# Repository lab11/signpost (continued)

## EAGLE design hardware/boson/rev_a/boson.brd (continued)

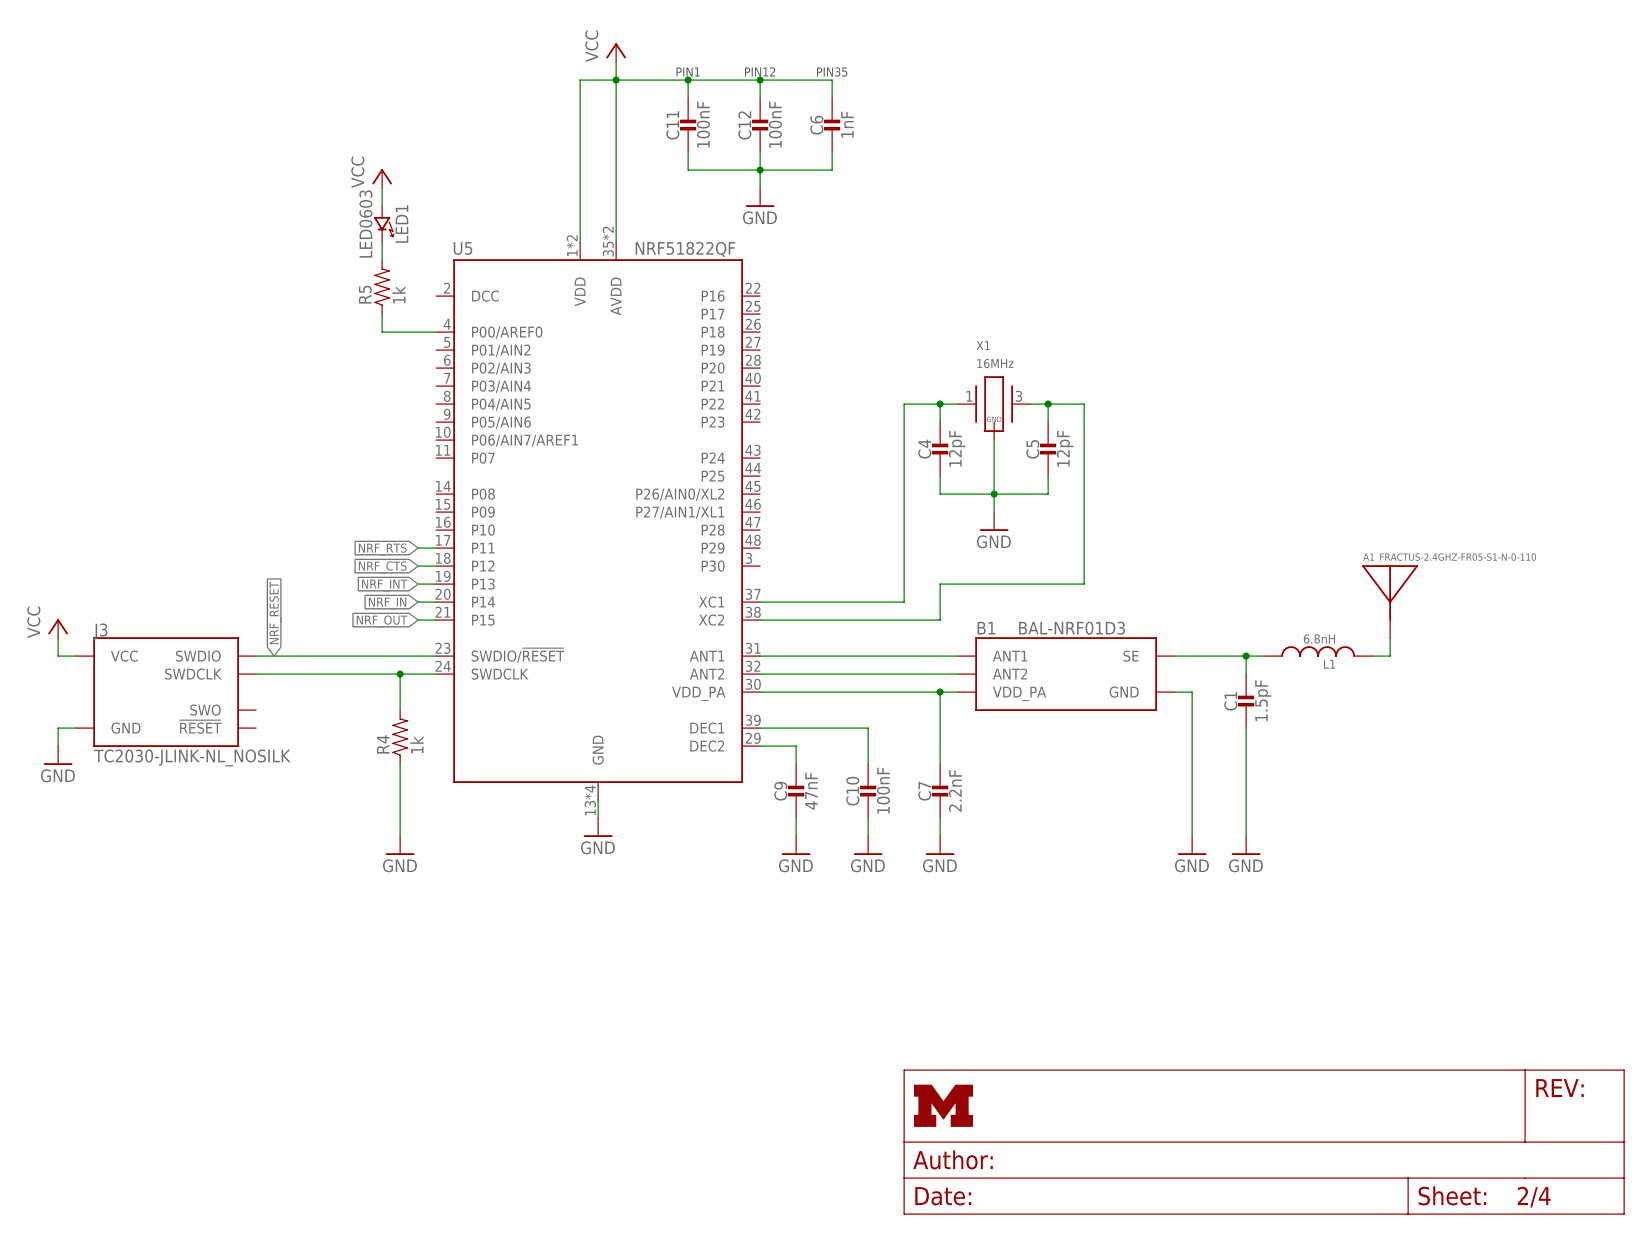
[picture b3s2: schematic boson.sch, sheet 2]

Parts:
A1: FRACTUS-2.4GHZ-FR05-S1-N-0-110; FRACTUS-ANTENNA-FR05-S1-N-0-110
B1: BAL-NRF01D3
C1: 1.5pF; 0402_CAP
C4, C5: 12pF; 0402_CAP; DIGIKEY 490-6197-1-ND
C6: 1nF; 0402_CAP
C7: 2.2nF; 0402_CAP
C9: 47nF; 0402_CAP
C10, C11, C12: 100nF; 0402_CAP
J3: TC2030-JLINK-NL_NOSILK; TC2030-IDC-NL_NOSILK
L1: 6.8nH; 0402_CAP
LED1: LED0603; LED-0603
R4, R5: 1k; 0402_RES
U5: NRF51822QF; QFN-48-6MM
X1: 16MHz; TXC-8Y; DIGIKEY 887-2003-1-ND

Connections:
!NRF_RESET: J3.2 (SWDIO), U5.23 (SWDIO/!RESET); also elsewhere on the board
GND: B1.GND, C1.2, C4.2, C5.2, C6.2, C7.2, C9.2, C10.2, C11.2, C12.2, J3.5 (GND), R4.1, U5.13 (GND), U5.33 (GND), U5.34 (GND), U5.GND, X1.2 (GND), X1.4 (GND); also elsewhere on the board
unnamed: C10.1, U5.39 (DEC1)
unnamed: C9.1, U5.29 (DEC2)
unnamed: J3.4 (SWDCLK), R4.2, U5.24 (SWDCLK)
unnamed: R5.1, U5.4 (P00/AREF0)
unnamed: LED1.C (CATHODE), R5.2
unnamed: B1.ANT1, U5.31 (ANT1)
unnamed: B1.VCC (VDD_PA), C7.1, U5.30 (VDD_PA)
unnamed: B1.ANT2, U5.32 (ANT2)
unnamed: C4.1, U5.37 (XC1), X1.1
unnamed: C5.1, U5.38 (XC2), X1.3 (2)
unnamed: B1.SE, C1.1, L1.1
unnamed: A1.ANT, L1.2
NRF_CTS: U5.18 (P12); also elsewhere on the board
NRF_IN: U5.20 (P14); also elsewhere on the board
NRF_INT: U5.19 (P13); also elsewhere on the board
NRF_OUT: U5.21 (P15); also elsewhere on the board
NRF_RTS: U5.17 (P11); also elsewhere on the board
VCC: C6.1, C11.1, C12.1, J3.1 (VCC), LED1.A (ANODE), U5.1 (VDD), U5.12 (VDD), U5.35 (AVDD), U5.36 (AVDD); also elsewhere on the board

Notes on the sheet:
PIN35
PIN1
PIN12

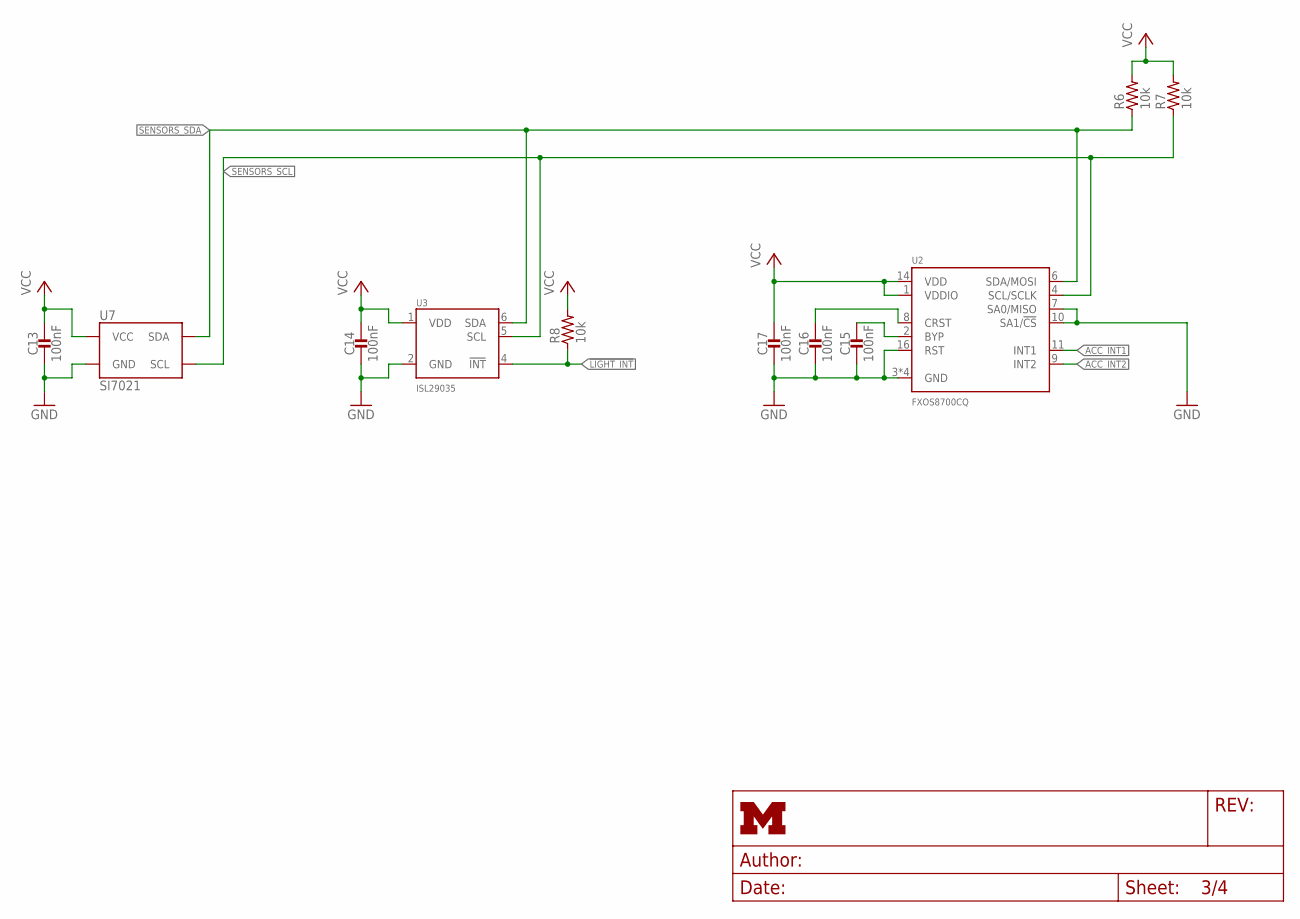
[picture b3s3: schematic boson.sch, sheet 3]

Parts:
C13, C14, C15, C16, C17: 100nF; 0402_CAP
R6, R7, R8: 10k; 0402_RES
U2: FXOS8700CQ; QFN-16-3MM
U3: ISL29035; ODFN-6-1.5MMX1.6MM
U7: SI7021; DFN-6/3MM

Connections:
!LIGHT_INT: R8.1, U3.4 (!INT); also elsewhere on the board
ACC_INT1: U2.11 (INT1); also elsewhere on the board
ACC_INT2: U2.9 (INT2); also elsewhere on the board
GND: C13.2, C14.2, C15.2, C16.2, C17.2, U2.3 (GND), U2.5 (GND), U2.7 (SA0/MISO), U2.10 (SA1/!CS), U2.12 (GND), U2.13 (GND), U2.16 (RST), U3.2 (GND), U7.2 (GND); also elsewhere on the board
unnamed: C15.1, U2.2 (BYP)
unnamed: C16.1, U2.8 (CRST)
SENSORS_SCL: R7.1, U2.4 (SCL/SCLK), U3.5 (SCL), U7.6 (SCL); also elsewhere on the board
SENSORS_SDA: R6.1, U2.6 (SDA/MOSI), U3.6 (SDA), U7.1 (SDA); also elsewhere on the board
VCC: C13.1, C14.1, C17.1, R6.2, R7.2, R8.2, U2.1 (VDDIO), U2.14 (VDD), U3.1 (VDD), U7.5 (VCC); also elsewhere on the board

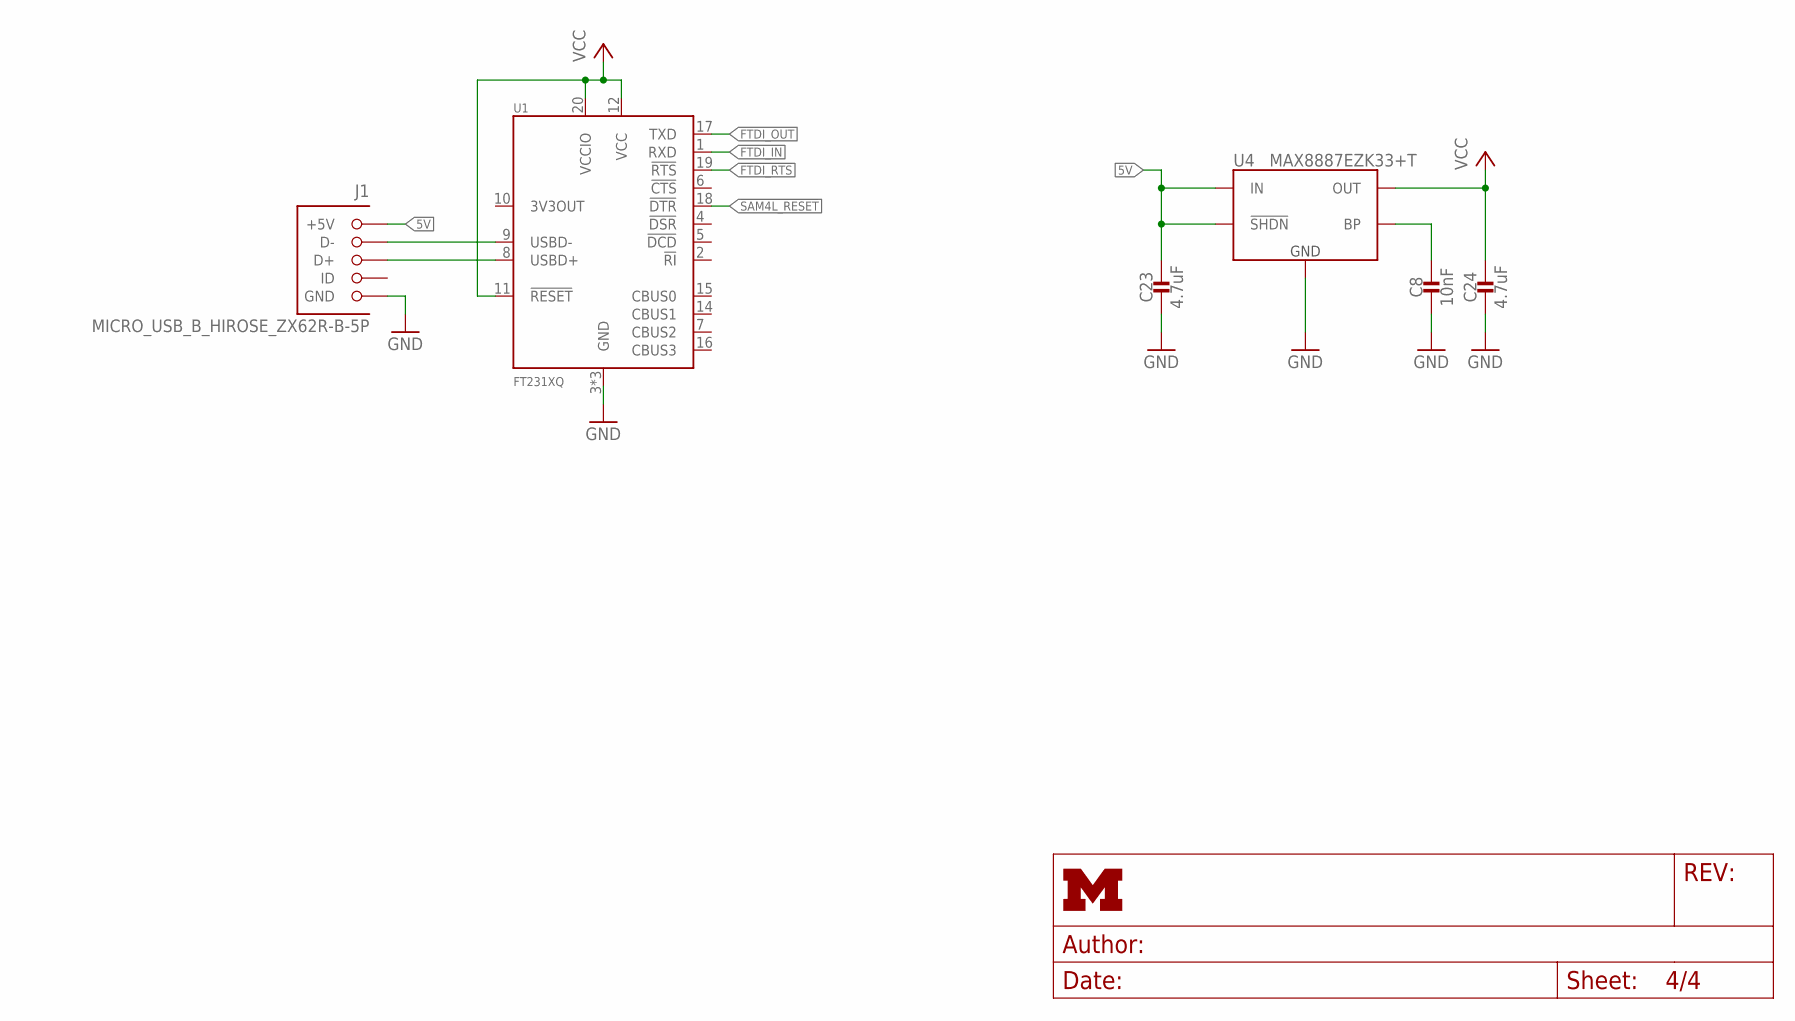
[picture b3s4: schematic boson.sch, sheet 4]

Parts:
C8: 10nF; 0402_CAP
C23, C24: 4.7uF; 0402_CAP
J1: MICRO_USB_B_HIROSE_ZX62R-B-5P; USB_MICRO_B-HIROSE-ZX62R-B-5P; DIGIKEY H125274CT-ND
U1: FT231XQ; QFN-20-4MM
U4: MAX8887EZK33+T; SOT-23-5

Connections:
5V: C23.1, J1.1 (+5V), U4.1 (IN), U4.3 (!SHDN); also elsewhere on the board
!FTDI_RTS: U1.19 (!RTS); also elsewhere on the board
!SAM4L_RESET: U1.18 (!DTR); also elsewhere on the board
FTDI_IN: U1.1 (RXD); also elsewhere on the board
FTDI_OUT: U1.17 (TXD); also elsewhere on the board
GND: C8.2, C23.2, C24.2, J1.5 (GND), U1.3 (GND), U1.13 (GND), U1.GND, U4.2 (GND); also elsewhere on the board
unnamed: J1.2 (D-), U1.9 (USBD-)
unnamed: J1.3 (D+), U1.8 (USBD+)
unnamed: C8.1, U4.4 (BP)
VCC: C24.1, U1.11 (!RESET), U1.12 (VCC), U1.20 (VCCIO), U4.5 (OUT); also elsewhere on the board

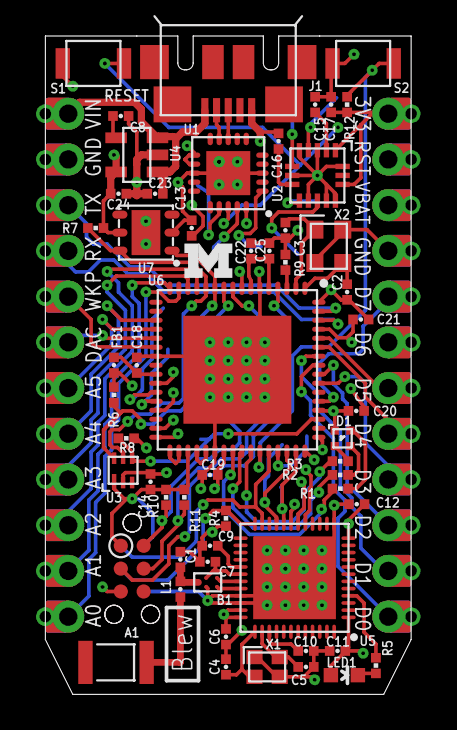
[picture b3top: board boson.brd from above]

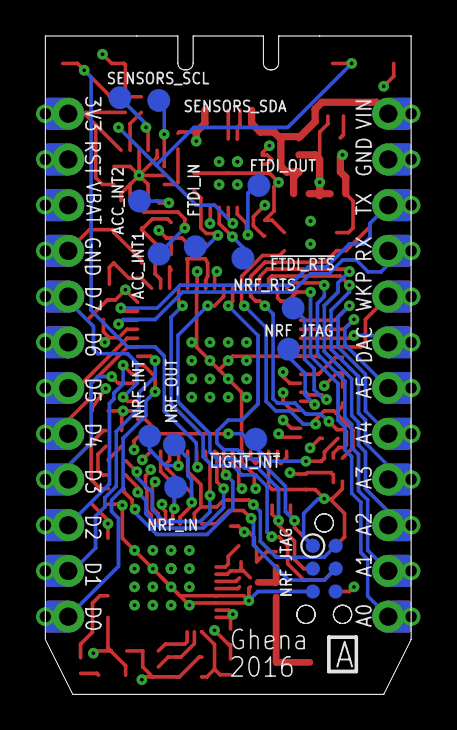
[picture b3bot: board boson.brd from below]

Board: 4 copper layers, 20.3 x 36.6 mm, 75 parts (14 on the bottom side), 69 nets.

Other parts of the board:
U$1: PHOTON-BOTTOM-SS
U$2: PHOTON-TOP-SS
U$3: UMICH_SOLID_75MIL

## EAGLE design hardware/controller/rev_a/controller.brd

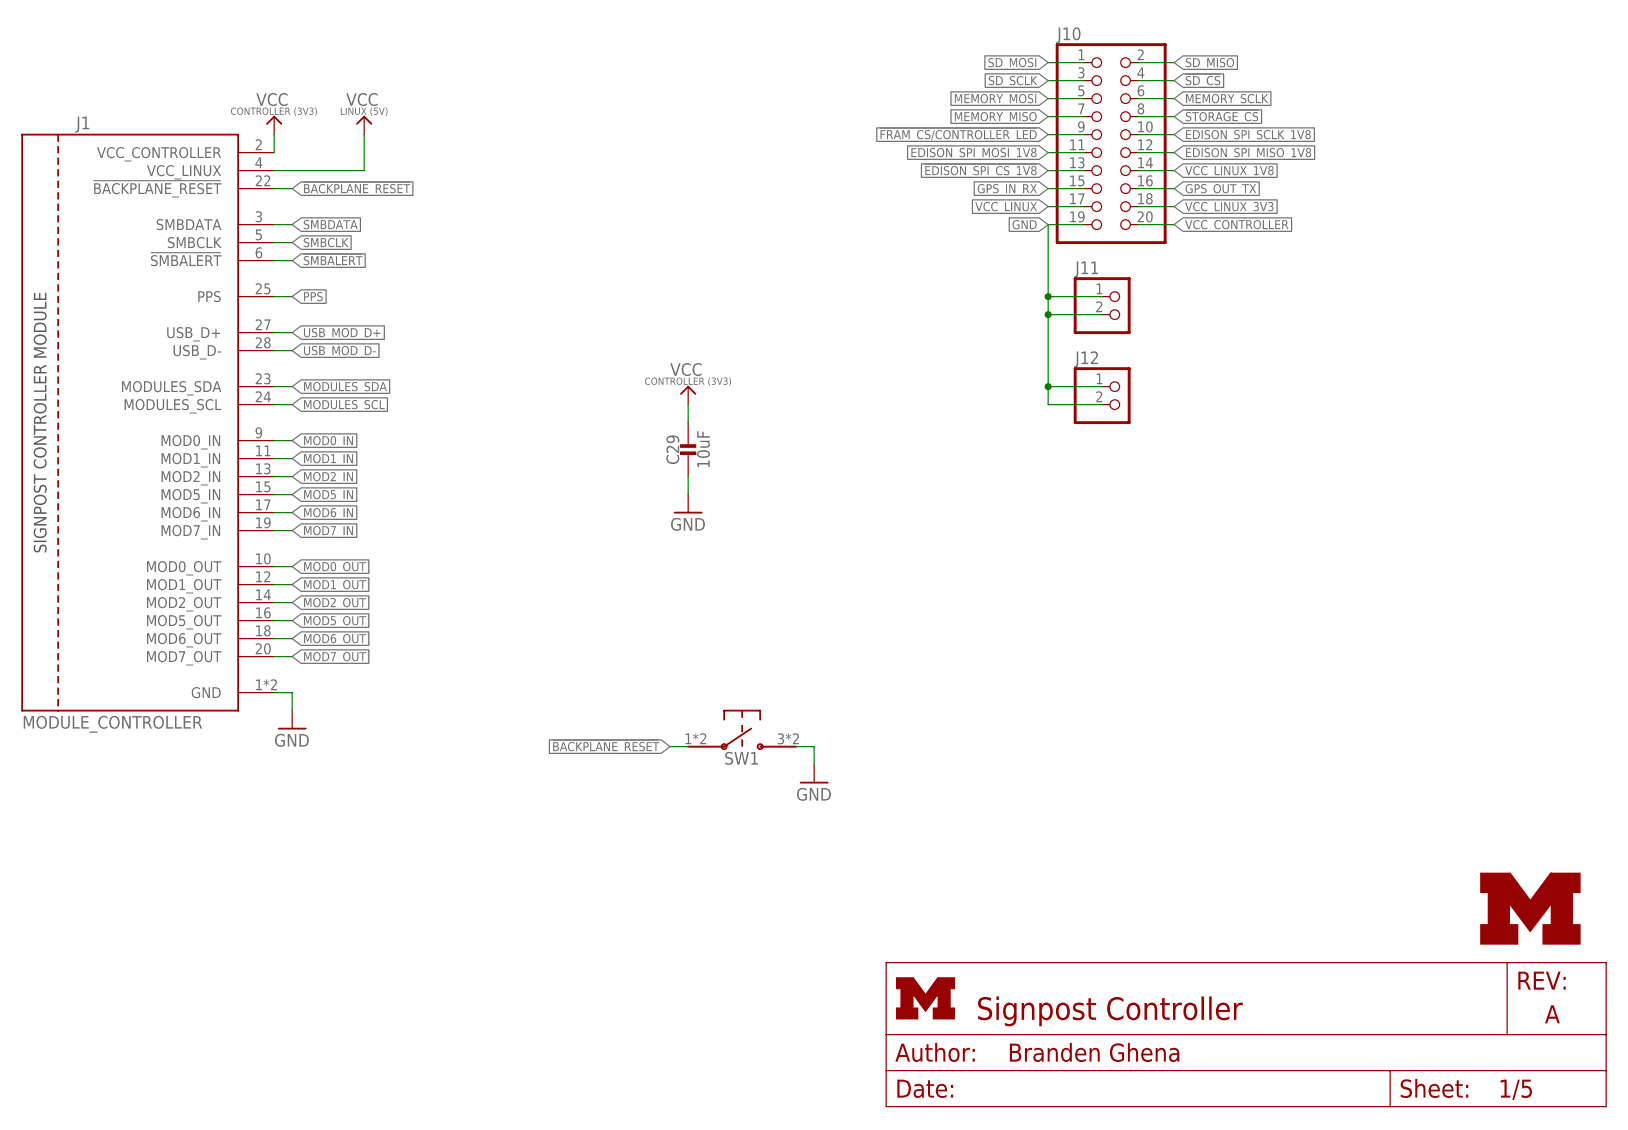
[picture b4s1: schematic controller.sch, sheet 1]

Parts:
C29: 10uF; 0402_CAP; DIGIKEY 490-13811-1-ND
J1: MODULE_CONTROLLER
J10: PINHD-2X10; 2X10
J11, J12: PINHD-1X2; 1X02
LOGO1: UMICH_SOLID_MEDIUM; UMICH_SOLID_200MIL
SW1: PTS810SJ

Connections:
!BACKPLANE_RESET: J1.22 (!BACKPLANE_RESET), SW1.1, SW1.2
!EDISON_SPI_CS_1V8: J10.13; also elsewhere on the board
!FRAM_CS/CONTROLLER_LED: J10.9; also elsewhere on the board
!SD_CS: J10.4; also elsewhere on the board
!SMBALERT: J1.6 (!SMBALERT); also elsewhere on the board
!STORAGE_CS: J10.8; also elsewhere on the board
EDISON_SPI_MISO_1V8: J10.12; also elsewhere on the board
EDISON_SPI_MOSI_1V8: J10.11; also elsewhere on the board
EDISON_SPI_SCLK_1V8: J10.10; also elsewhere on the board
GND: C29.2, J1.1 (GND), J1.21 (GND), J10.19, J11.1, J11.2, J12.1, J12.2, SW1.3, SW1.4; also elsewhere on the board
GPS_IN_RX: J10.15; also elsewhere on the board
GPS_OUT_TX: J10.16; also elsewhere on the board
MEMORY_MISO: J10.7; also elsewhere on the board
MEMORY_MOSI: J10.5; also elsewhere on the board
MEMORY_SCLK: J10.6; also elsewhere on the board
MOD0_IN: J1.9 (MOD0_IN); also elsewhere on the board
MOD0_OUT: J1.10 (MOD0_OUT); also elsewhere on the board
MOD1_IN: J1.11 (MOD1_IN); also elsewhere on the board
MOD1_OUT: J1.12 (MOD1_OUT); also elsewhere on the board
MOD2_IN: J1.13 (MOD2_IN); also elsewhere on the board
MOD2_OUT: J1.14 (MOD2_OUT); also elsewhere on the board
MOD5_IN: J1.15 (MOD5_IN); also elsewhere on the board
MOD5_OUT: J1.16 (MOD5_OUT); also elsewhere on the board
MOD6_IN: J1.17 (MOD6_IN); also elsewhere on the board
MOD6_OUT: J1.18 (MOD6_OUT); also elsewhere on the board
MOD7_IN: J1.19 (MOD7_IN); also elsewhere on the board
MOD7_OUT: J1.20 (MOD7_OUT); also elsewhere on the board
MODULES_SCL: J1.24 (MODULES_SCL); also elsewhere on the board
MODULES_SDA: J1.23 (MODULES_SDA); also elsewhere on the board
PPS: J1.25 (PPS); also elsewhere on the board
SD_MISO: J10.2; also elsewhere on the board
SD_MOSI: J10.1; also elsewhere on the board
SD_SCLK: J10.3; also elsewhere on the board
SMBCLK: J1.5 (SMBCLK); also elsewhere on the board
SMBDATA: J1.3 (SMBDATA); also elsewhere on the board
USB_MOD_D+: J1.27 (USB_D+); also elsewhere on the board
USB_MOD_D-: J1.28 (USB_D-); also elsewhere on the board
VCC_CONTROLLER: C29.1, J1.2 (VCC_CONTROLLER), J10.20; also elsewhere on the board
VCC_LINUX: J1.4 (VCC_LINUX), J10.17; also elsewhere on the board
VCC_LINUX_1V8: J10.14; also elsewhere on the board
VCC_LINUX_3V3: J10.18; also elsewhere on the board

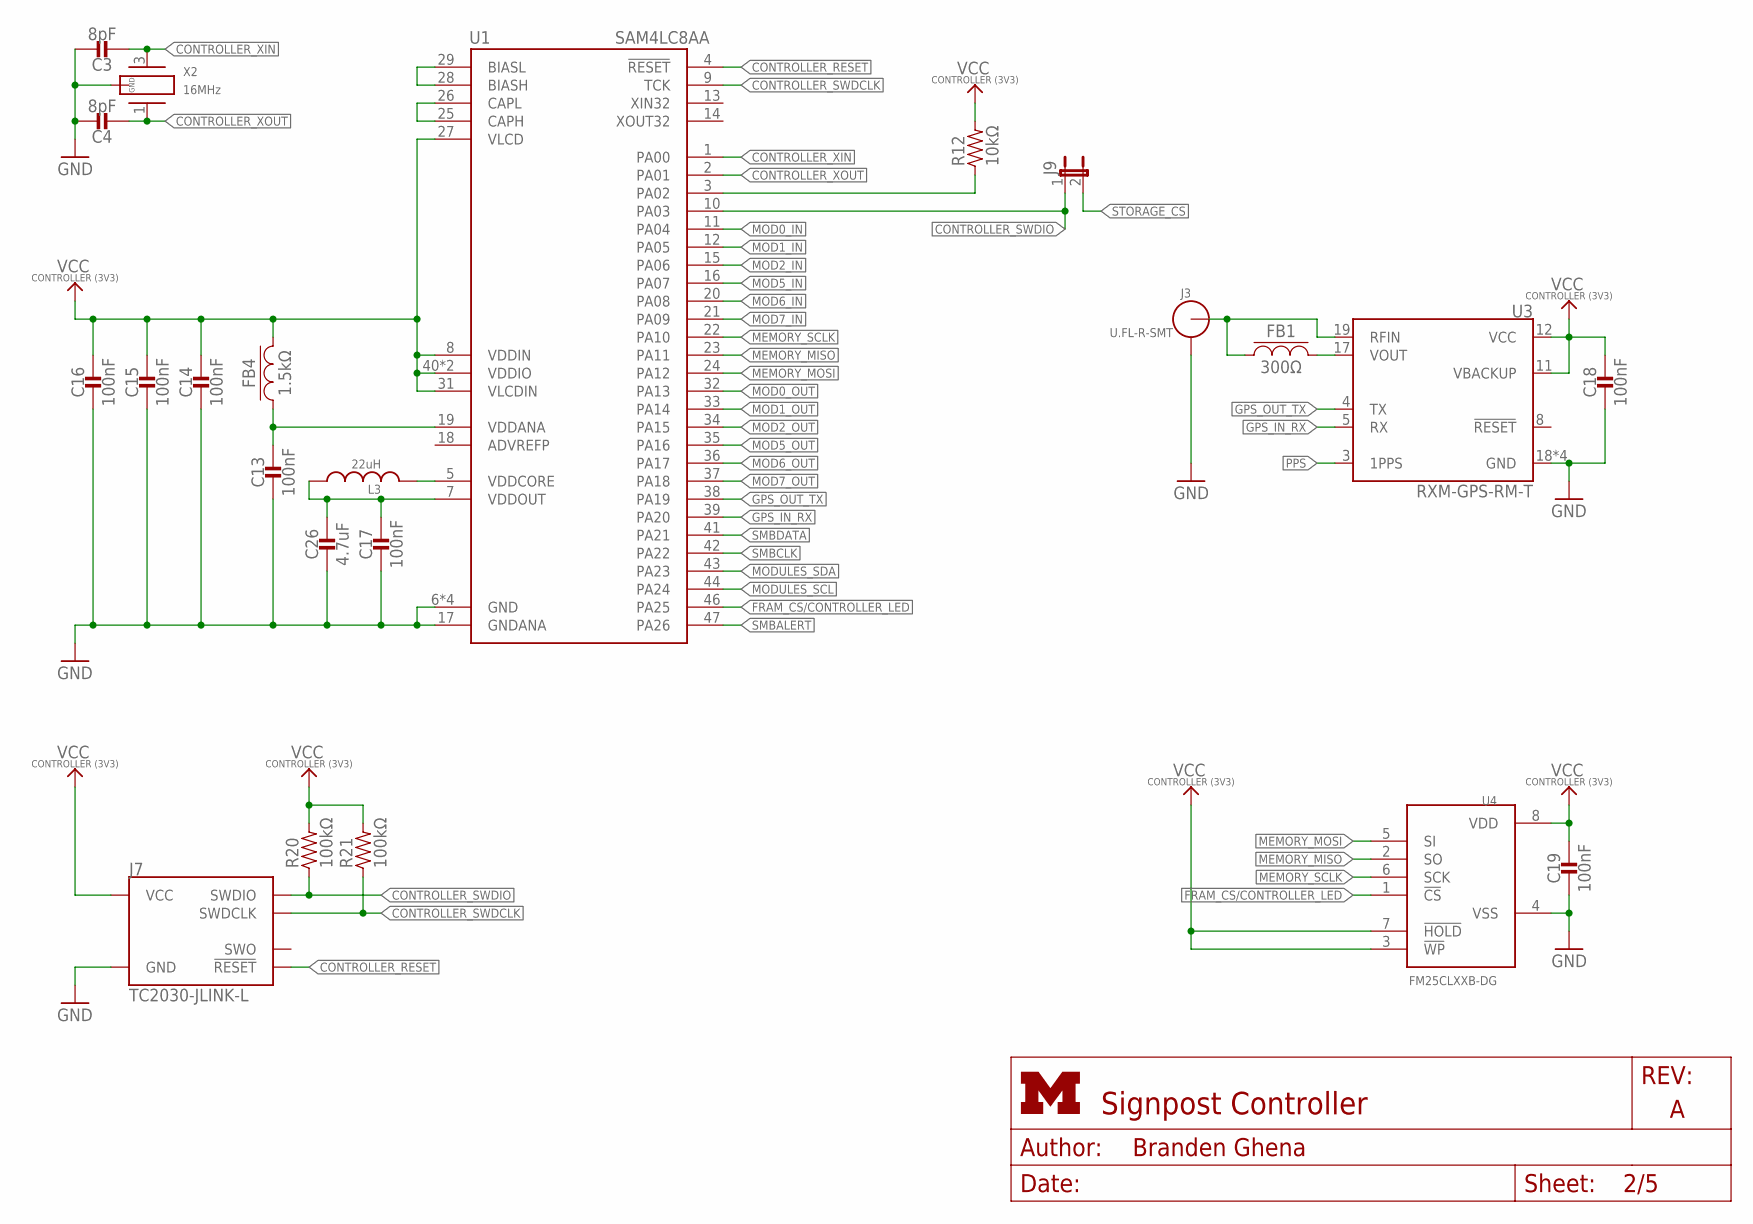
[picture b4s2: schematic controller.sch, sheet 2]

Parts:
C3, C4: 8pF; 0402_CAP; DIGIKEY 490-8230-1-ND
C13, C14, C15, C16, C17, C18, C19: 100nF; 0402_CAP; DIGIKEY 490-10777-1-ND
C26: 4.7uF; 0402_CAP; DIGIKEY 490-13252-1-ND
FB1: 300Ω; 0402_CAP; DIGIKEY ACML-0402-301-TCT-ND
FB4: 1.5kΩ; 0402_CAP; DIGIKEY 490-5216-1-ND
J3: U.FL-R-SMT; U.FL_SMT
J7: TC2030-JLINK-L; TC2030-IDC
J9: JUMPER-2PTH; 1X02
L3: 22uH; 1212
R12: 10kΩ; 0402_RES; DIGIKEY 1276-3431-1-ND
R20, R21: 100kΩ; 0402_RES; DIGIKEY 1276-3432-1-ND
U1: SAM4LC8AA; QFN-48-7MM
U3: RXM-GPS-RM-T
U4: FM25CLXXB-DG; TDFN-8; DIGIKEY FM25CL64B-DGRA-ND
X2: 16MHz; FHXXX

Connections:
!CONTROLLER_RESET: J7.3 (!RESET), U1.4 (!RESET)
!FRAM_CS/CONTROLLER_LED: U1.46 (PA25), U4.1 (!CS); also elsewhere on the board
!SMBALERT: U1.47 (PA26); also elsewhere on the board
!STORAGE_CS: J9.2; also elsewhere on the board
CONTROLLER_BUCK/LDO_N: R12.1, U1.3 (PA02)
CONTROLLER_SWDCLK: J7.4 (SWDCLK), R21.1, U1.9 (TCK)
CONTROLLER_SWDIO: J7.2 (SWDIO), J9.1, R20.1, U1.10 (PA03)
CONTROLLER_XIN: C3.1, U1.1 (PA00), X2.3 (2)
CONTROLLER_XOUT: C4.1, U1.2 (PA01), X2.1
GND: C3.2, C4.2, C13.2, C14.2, C15.2, C16.2, C17.2, C18.2, C19.2, C26.2, J3.GND1, J3.GND2, J7.5 (GND), U1.6 (GND), U1.17 (GNDANA), U1.30 (GND), U1.48 (GND), U1.THERMAL (GND), U3.18 (GND), U3.20 (GND), U3.21 (GND), U3.22 (GND), U4.4 (VSS), X2.2 (GND), X2.4 (GND); also elsewhere on the board
GPS_IN_RX: U1.39 (PA20), U3.5 (RX); also elsewhere on the board
GPS_OUT_TX: U1.38 (PA19), U3.4 (TX); also elsewhere on the board
MEMORY_MISO: U1.23 (PA11), U4.2 (SO); also elsewhere on the board
MEMORY_MOSI: U1.24 (PA12), U4.5 (SI); also elsewhere on the board
MEMORY_SCLK: U1.22 (PA10), U4.6 (SCK); also elsewhere on the board
MOD0_IN: U1.11 (PA04); also elsewhere on the board
MOD0_OUT: U1.32 (PA13); also elsewhere on the board
MOD1_IN: U1.12 (PA05); also elsewhere on the board
MOD1_OUT: U1.33 (PA14); also elsewhere on the board
MOD2_IN: U1.15 (PA06); also elsewhere on the board
MOD2_OUT: U1.34 (PA15); also elsewhere on the board
MOD5_IN: U1.16 (PA07); also elsewhere on the board
MOD5_OUT: U1.35 (PA16); also elsewhere on the board
MOD6_IN: U1.20 (PA08); also elsewhere on the board
MOD6_OUT: U1.36 (PA17); also elsewhere on the board
MOD7_IN: U1.21 (PA09); also elsewhere on the board
MOD7_OUT: U1.37 (PA18); also elsewhere on the board
MODULES_SCL: U1.44 (PA24); also elsewhere on the board
MODULES_SDA: U1.43 (PA23); also elsewhere on the board
unnamed: FB1.1, U3.17 (VOUT)
unnamed: FB1.2, J3.SIG (ANT), U3.19 (RFIN)
unnamed: C13.1, FB4.1, U1.19 (VDDANA)
unnamed: C17.1, C26.1, L3.P$1 (1), U1.7 (VDDOUT)
unnamed: L3.P$2 (2), U1.5 (VDDCORE)
unnamed: U1.28 (BIASH), U1.29 (BIASL)
unnamed: U1.25 (CAPH), U1.26 (CAPL)
PPS: U3.3 (1PPS); also elsewhere on the board
SMBCLK: U1.42 (PA22); also elsewhere on the board
SMBDATA: U1.41 (PA21); also elsewhere on the board
VCC_CONTROLLER: C14.1, C15.1, C16.1, C18.1, C19.1, FB4.2, J7.1 (VCC), R12.2, R20.2, R21.2, U1.8 (VDDIN), U1.27 (VLCD), U1.31 (VLCDIN), U1.40 (VDDIO), U1.45 (VDDIO), U3.11 (VBACKUP), U3.12 (VCC), U4.3 (!WP), U4.7 (!HOLD), U4.8 (VDD); also elsewhere on the board

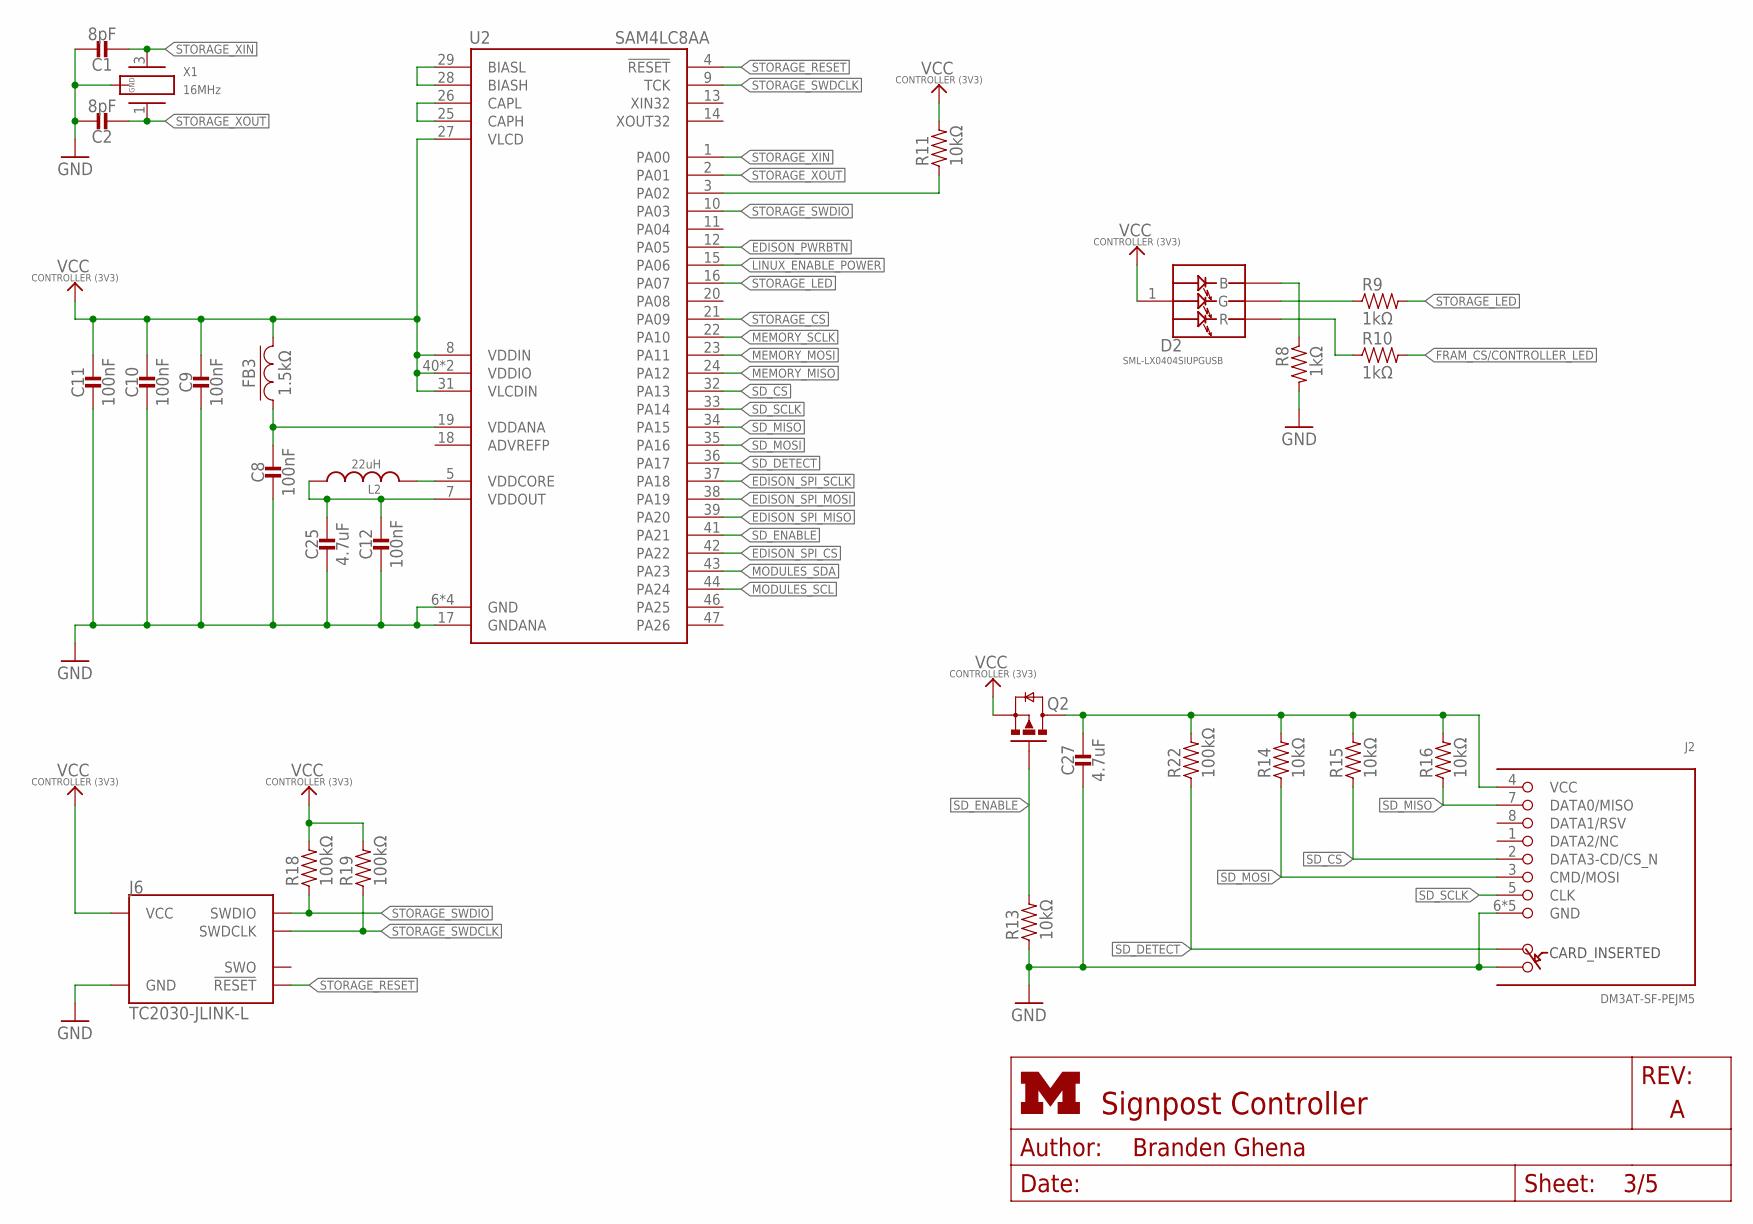
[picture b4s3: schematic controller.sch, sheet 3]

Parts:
C1, C2: 8pF; 0402_CAP; DIGIKEY 490-8230-1-ND
C8, C9, C10, C11, C12: 100nF; 0402_CAP; DIGIKEY 490-10777-1-ND
C25, C27: 4.7uF; 0402_CAP; DIGIKEY 490-13252-1-ND
D2: SML-LX0404SIUPGUSB; 1MM_SQ_4PAD
FB3: 1.5kΩ; 0402_CAP; DIGIKEY 490-5216-1-ND
J2: DM3AT-SF-PEJM5
J6: TC2030-JLINK-L; TC2030-IDC
L2: 22uH; 1212
Q2: NX3008PBK; SOT23-3
R8, R9, R10: 1kΩ; 0402_RES; DIGIKEY 1276-3430-1-ND
R11, R13, R14, R15, R16: 10kΩ; 0402_RES; DIGIKEY 1276-3431-1-ND
R18, R19, R22: 100kΩ; 0402_RES; DIGIKEY 1276-3432-1-ND
U2: SAM4LC8AA; QFN-48-7MM
X1: 16MHz; FHXXX

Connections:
!EDISON_PWRBTN: U2.12 (PA05); also elsewhere on the board
!EDISON_SPI_CS: U2.42 (PA22); also elsewhere on the board
!FRAM_CS/CONTROLLER_LED: R10.2; also elsewhere on the board
!SD_CS: J2.2 (DATA3-CD/CS_N), R15.1, U2.32 (PA13); also elsewhere on the board
!STORAGE_CS: U2.21 (PA09); also elsewhere on the board
!STORAGE_LED: R9.2, U2.16 (PA07)
!STORAGE_RESET: J6.3 (!RESET), U2.4 (!RESET)
EDISON_SPI_MISO: U2.39 (PA20); also elsewhere on the board
EDISON_SPI_MOSI: U2.38 (PA19); also elsewhere on the board
EDISON_SPI_SCLK: U2.37 (PA18); also elsewhere on the board
GND: C1.2, C2.2, C8.2, C9.2, C10.2, C11.2, C12.2, C25.2, C27.2, J2.6 (GND), J2.B, J2.MOUNT0 (GND), J2.MOUNT1 (GND), J2.MOUNT2 (GND), J2.MOUNT3 (GND), J6.5 (GND), R8.2, R13.1, U2.6 (GND), U2.17 (GNDANA), U2.30 (GND), U2.48 (GND), U2.THERMAL (GND), X1.2 (GND), X1.4 (GND); also elsewhere on the board
LINUX_ENABLE_POWER: U2.15 (PA06); also elsewhere on the board
MEMORY_MISO: U2.24 (PA12); also elsewhere on the board
MEMORY_MOSI: U2.23 (PA11); also elsewhere on the board
MEMORY_SCLK: U2.22 (PA10); also elsewhere on the board
MODULES_SCL: U2.44 (PA24); also elsewhere on the board
MODULES_SDA: U2.43 (PA23); also elsewhere on the board
unnamed: D2.3 (B), R8.1
unnamed: D2.4 (G), R9.1
unnamed: D2.2 (R), R10.1
unnamed: C27.1, J2.4 (VCC), Q2.3 (D), R14.2, R15.2, R16.2, R22.2
unnamed: C8.1, FB3.1, U2.19 (VDDANA)
unnamed: C12.1, C25.1, L2.P$1 (1), U2.7 (VDDOUT)
unnamed: L2.P$2 (2), U2.5 (VDDCORE)
unnamed: U2.25 (CAPH), U2.26 (CAPL)
unnamed: U2.28 (BIASH), U2.29 (BIASL)
SD_DETECT: J2.A, R22.1, U2.36 (PA17)
SD_ENABLE: Q2.1 (G), R13.2, U2.41 (PA21)
SD_MISO: J2.7 (DATA0/MISO), R16.1, U2.34 (PA15); also elsewhere on the board
SD_MOSI: J2.3 (CMD/MOSI), R14.1, U2.35 (PA16); also elsewhere on the board
SD_SCLK: J2.5 (CLK), U2.33 (PA14); also elsewhere on the board
STORAGE_BUCK/LDO_N: R11.1, U2.3 (PA02)
STORAGE_SWDCLK: J6.4 (SWDCLK), R19.1, U2.9 (TCK)
STORAGE_SWDIO: J6.2 (SWDIO), R18.1, U2.10 (PA03)
STORAGE_XIN: C1.1, U2.1 (PA00), X1.3 (2)
STORAGE_XOUT: C2.1, U2.2 (PA01), X1.1
VCC_CONTROLLER: C9.1, C10.1, C11.1, D2.1 (VDD), FB3.2, J6.1 (VCC), Q2.2 (S), R11.2, R18.2, R19.2, U2.8 (VDDIN), U2.27 (VLCD), U2.31 (VLCDIN), U2.40 (VDDIO), U2.45 (VDDIO); also elsewhere on the board

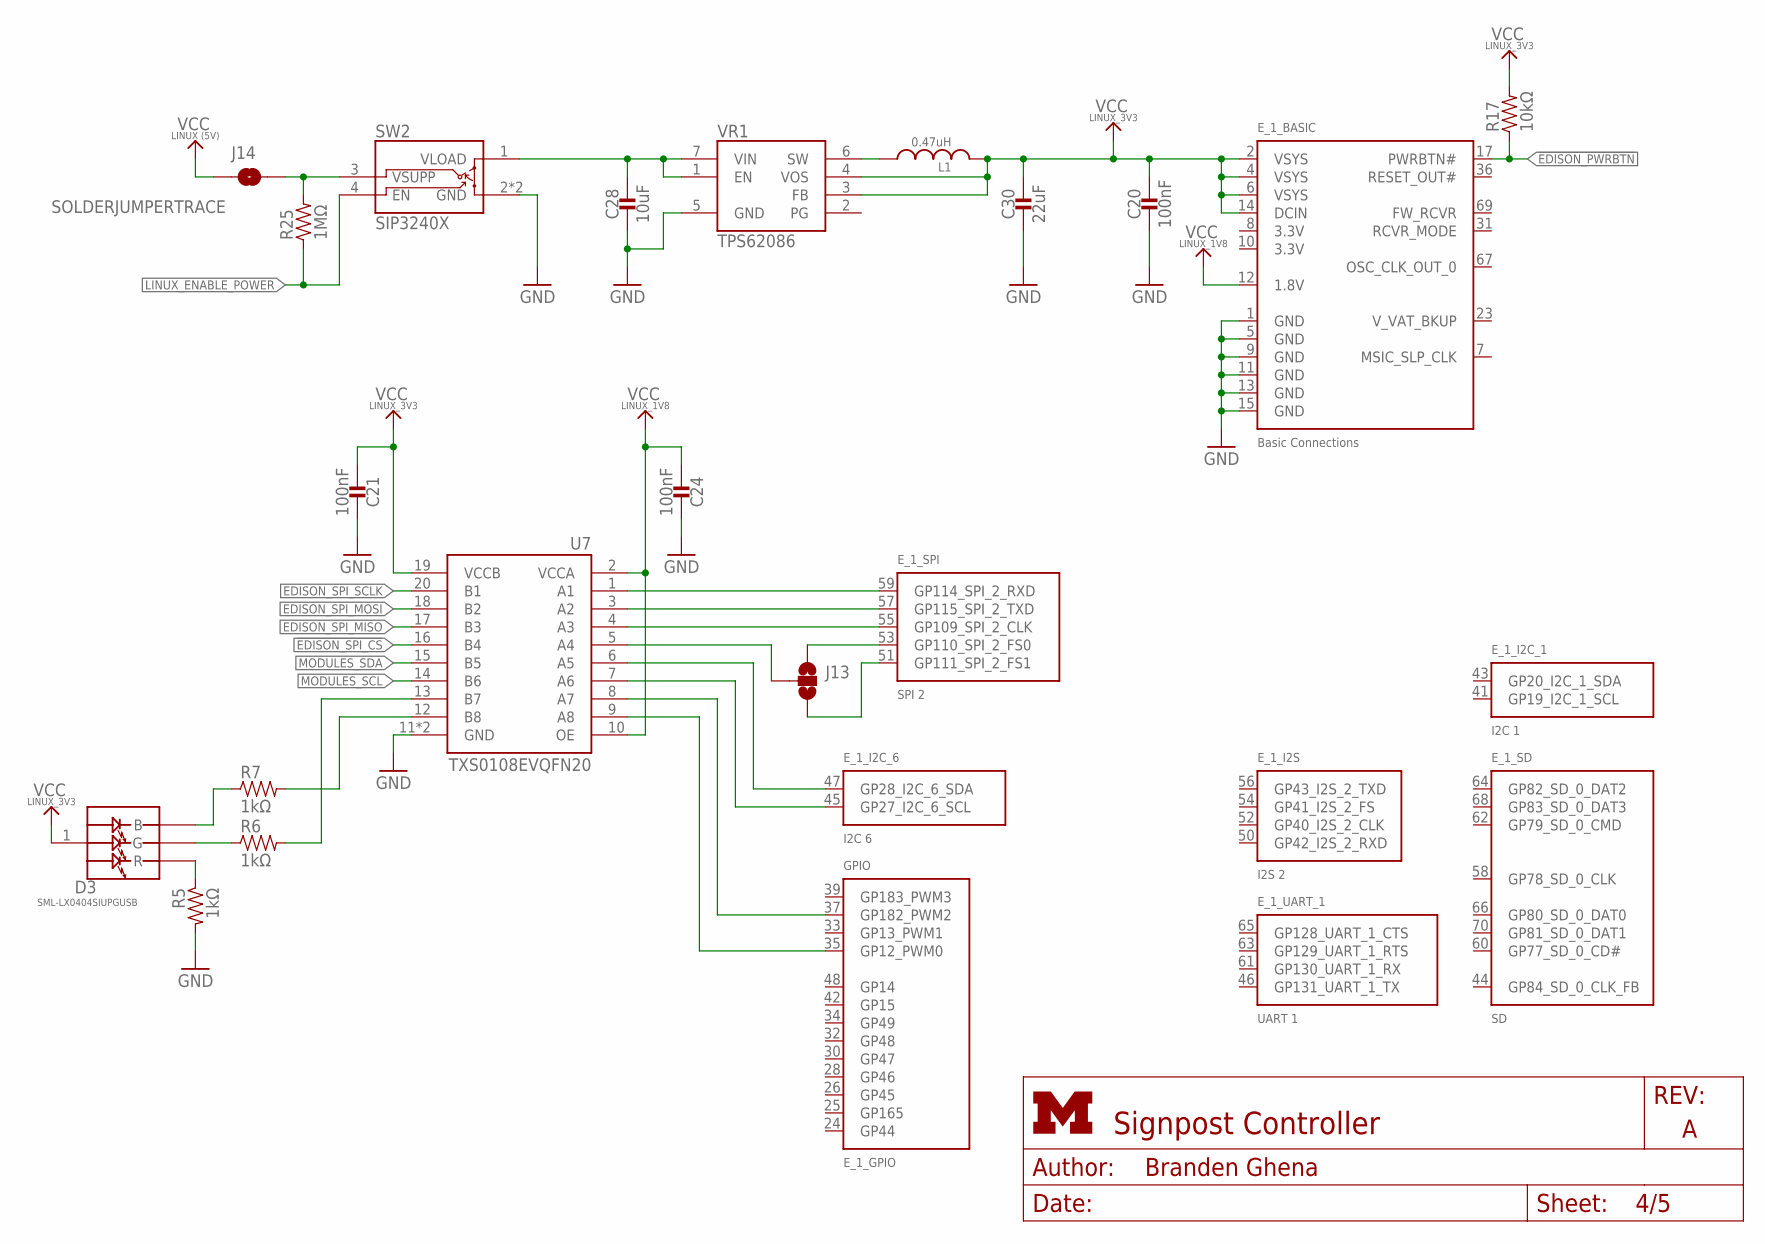
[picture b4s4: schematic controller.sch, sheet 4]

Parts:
C20, C21, C24: 100nF; 0402_CAP; DIGIKEY 490-10777-1-ND
C28: 10uF; 0805_CAP; DIGIKEY 490-8316-1-ND
C30: 22uF; 0805_CAP; DIGIKEY 490-1719-1-ND
D3: SML-LX0404SIUPGUSB; 1MM_SQ_4PAD
E_1: EDISON_CONNECTOR_SEGMENTED; EDISON_DAUGHTER; MOUSER 798-DF40HC3070DS4V51
J13: SOLDERJUMPER_2WAYPASTE2&3; SJ_3_PASTE2&3
J14: SOLDERJUMPERTRACE; SJ_2S-TRACE
L1: 0.47uH; DFE322512C; MOUSER 81-1277AS-H-R47MP2
R5, R6, R7: 1kΩ; 0402_RES; DIGIKEY 1276-3430-1-ND
R17: 10kΩ; 0402_RES; DIGIKEY 1276-3431-1-ND
R25: 1MΩ; 0402_RES; DIGIKEY 1276-3433-1-ND
SW2: SIP3240X; TDFN4
U7: TXS0108EVQFN20; R-PVQFN-N20; DIGIKEY 296-24806-1-ND
VR1: TPS62086; RLT0007A

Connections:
!EDISON_PWRBTN: E_1.17 (PWRBTN#), R17.1; also elsewhere on the board
!EDISON_SPI_CS: U7.16 (B4); also elsewhere on the board
!EDISON_SPI_CS_1V8: J13.2, U7.5 (A4); also elsewhere on the board
EDISON_SPI_MISO: U7.17 (B3); also elsewhere on the board
EDISON_SPI_MISO_1V8: E_1.55 (GP109_SPI_2_CLK), U7.4 (A3); also elsewhere on the board
EDISON_SPI_MOSI: U7.18 (B2); also elsewhere on the board
EDISON_SPI_MOSI_1V8: E_1.57 (GP115_SPI_2_TXD), U7.3 (A2); also elsewhere on the board
EDISON_SPI_SCLK: U7.20 (B1); also elsewhere on the board
EDISON_SPI_SCLK_1V8: E_1.59 (GP114_SPI_2_RXD), U7.1 (A1); also elsewhere on the board
GND: C20.2, C21.1, C24.1, C28.P$2 (2), C30.P$2 (2), E_1.1 (GND), E_1.5 (GND), E_1.9 (GND), E_1.11 (GND), E_1.13 (GND), E_1.15 (GND), R5.2, SW2.2 (GND), SW2.PAD (GND), U7.11 (GND), U7.THERMAL (GND), VR1.5 (GND); also elsewhere on the board
LINUX_5V_IN: C28.P$1 (1), SW2.1 (VLOAD), VR1.1 (EN), VR1.7 (VIN)
LINUX_ENABLE_POWER: R25.1, SW2.4 (EN); also elsewhere on the board
MODULES_SCL: U7.14 (B6); also elsewhere on the board
MODULES_SCL_1V8: E_1.45 (GP27_I2C_6_SCL), U7.7 (A6)
MODULES_SDA: U7.15 (B5); also elsewhere on the board
MODULES_SDA_1V8: E_1.47 (GP28_I2C_6_SDA), U7.6 (A5)
unnamed: E_1.53 (GP110_SPI_2_FS0), J13.1
unnamed: R7.2, U7.12 (B8)
unnamed: E_1.51 (GP111_SPI_2_FS1), J13.3
unnamed: L1.P$1 (1), VR1.6 (SW)
unnamed: J14.2, R25.2, SW2.3 (VSUPP)
unnamed: E_1.37 (GP182_PWM2), U7.8 (A7)
unnamed: D3.2 (R), R5.1
unnamed: D3.4 (G), R6.1
unnamed: D3.3 (B), R7.1
unnamed: E_1.35 (GP12_PWM0), U7.9 (A8)
unnamed: R6.2, U7.13 (B7)
VCC_LINUX: J14.1; also elsewhere on the board
VCC_LINUX_1V8: C24.2, E_1.12 (1.8V), U7.2 (VCCA), U7.10 (OE); also elsewhere on the board
VCC_LINUX_3V3: C20.1, C21.2, C30.P$1 (1), D3.1 (VDD), E_1.2 (VSYS), E_1.4 (VSYS), E_1.6 (VSYS), E_1.14 (DCIN), L1.P$2 (2), R17.2, U7.19 (VCCB), VR1.3 (FB), VR1.4 (VOS); also elsewhere on the board
